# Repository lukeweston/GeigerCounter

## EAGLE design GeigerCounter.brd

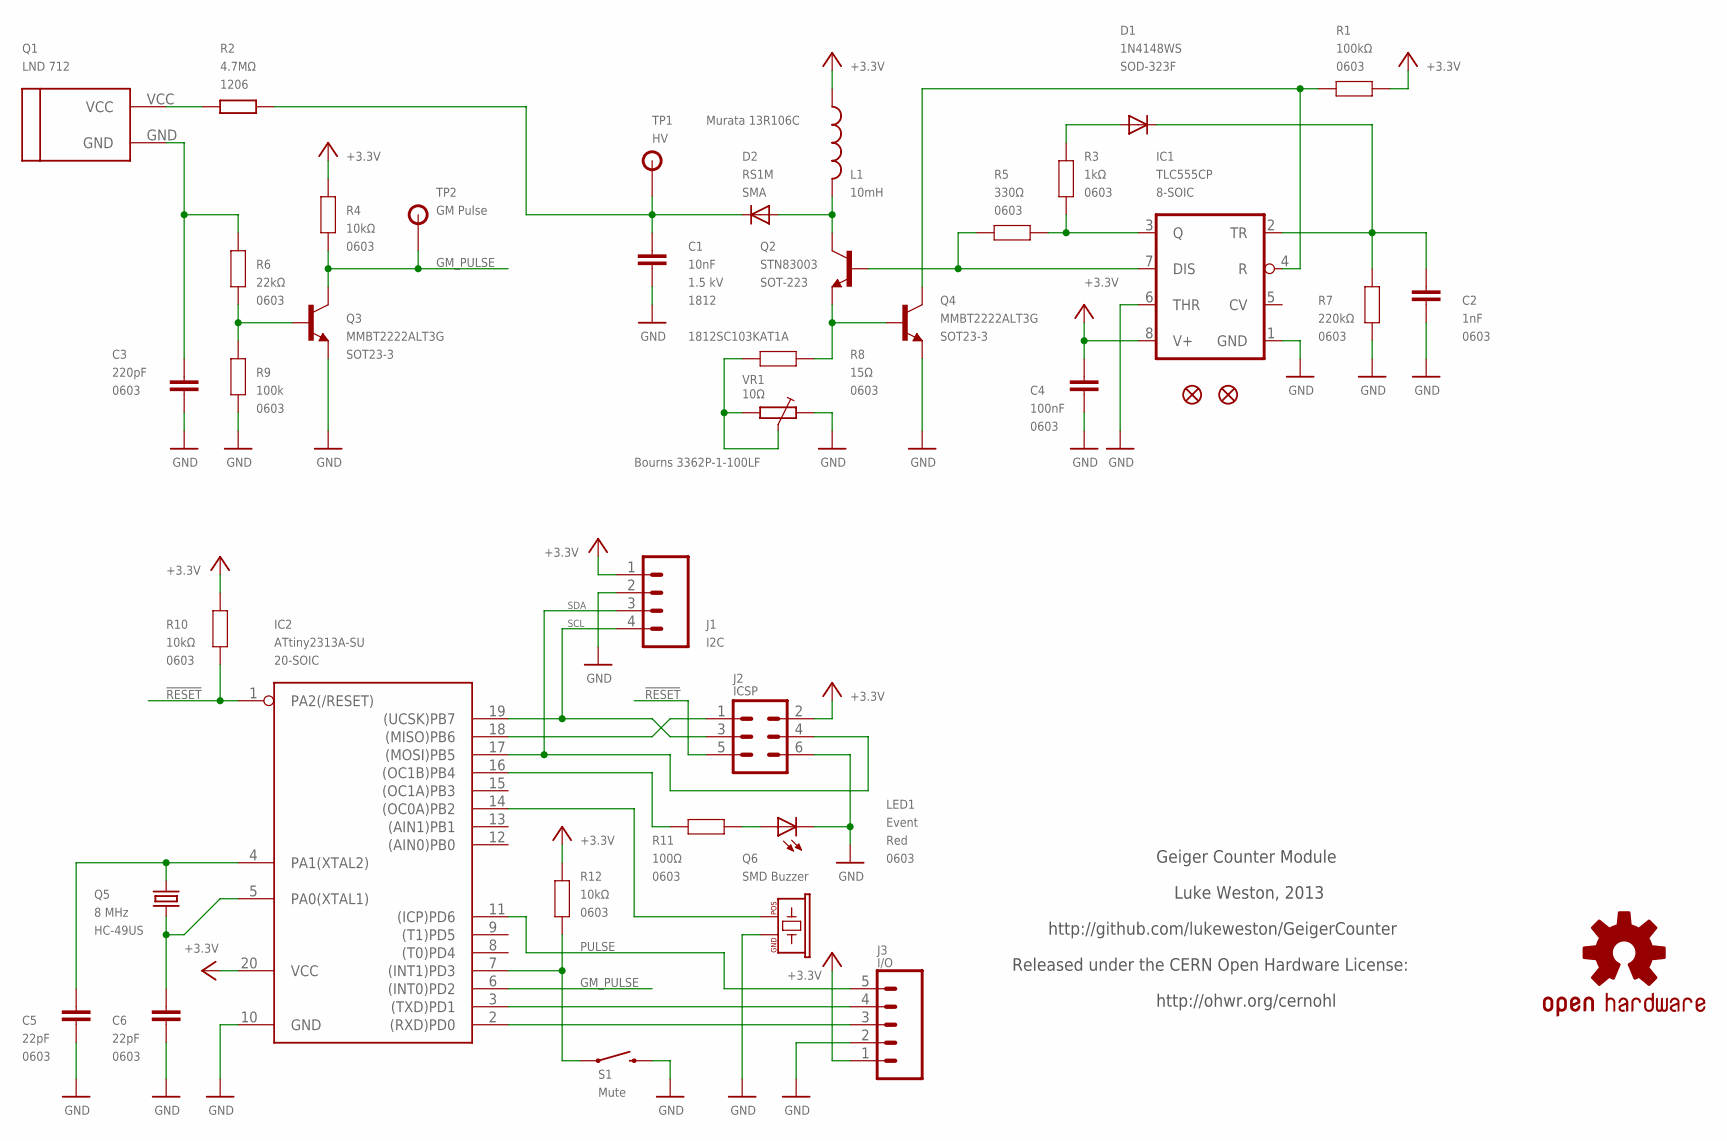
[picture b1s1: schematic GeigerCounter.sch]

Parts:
C1: 10nF; C1812; VOLTAGE 1.5 kV
C2: 1nF; 0603
C3: 220pF; 0603
C4: 100nF; 0603
C5, C6: 22pF; 0603
D1: 1N4148WS; SOD-323
D2: RS1M; DO214AC
IC1: TLC555CP; SO08
IC2: ATtiny2313A-SU; SO20L$
J1: I2C; 1X04
J2: ICSP; ICSP-6
J3: I/O; 1X05
JP1, JP2: FIDUCIALUFIDUCIAL; MICRO-FIDUCIAL
L1: 10mH; INDUCTOR-5.08
LED1: Event; LED-0603
Q1: LND 712; GEIGER_TUBE
Q2: STN83003; SOT223
Q3, Q4: MMBT2222ALT3G; SOT23
Q5: 8 MHz; HC49US
Q6: SMD Buzzer; BUZZER-12X12-SMT
R1: 100kΩ; 0603
R2: 4.7MΩ; R1206
R3: 1kΩ; 0603
R4, R10, R12: 10kΩ; 0603
R5: 330Ω; 0603
R6: 22kΩ; 0603
R7: 220kΩ; 0603
R8: 15Ω; 0603
R9: 100k; 0603
R11: 100Ω; 0603
S1: Mute; TACTILE_SWITCH_SMD
SY: OSHW-LOGOS; OSHW-LOGO-S
TP1: HV; TP_PTH
TP2: GM Pulse; TP_PTH
VR1: 10Ω; CT6

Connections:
!RESET: IC2.1 (PA2(/RESET)), J2.5, R10.1
+3V3: C4.1, IC1.8 (V+), IC2.20 (VCC), J1.1, J2.2, J3.1, L1.1, R1.1, R4.2, R10.2, R12.1
GM_PULSE: IC2.6 ((INT0)PD2), Q3.3 (C), R4.1, TP2.P$1
GND: C1.2, C2.2, C3.2, C4.2, C5.2, C6.2, IC1.1 (GND), IC1.6 (THR), IC2.10 (GND), J1.2, J2.6, J3.2, LED1.C, Q3.2 (E), Q4.2 (E), Q6.1 (GND), R7.1, R9.1, S1.3 (2), VR1.E
MUTE1: IC2.7 ((INT1)PD3), R12.2, S1.1
unnamed: Q1.VCC, R2.1
unnamed: IC1.7 (DIS), Q2.1 (B), R5.2
unnamed: IC1.4 (R), Q4.3 (C), R1.2
unnamed: IC2.2 ((RXD)PD0), J3.3
unnamed: IC2.3 ((TXD)PD1), J3.4
unnamed: C6.1, IC2.5 (PA0(XTAL1)), Q5.1
unnamed: C5.1, IC2.4 (PA1(XTAL2)), Q5.2
unnamed: IC2.18 ((MISO)PB6), J2.1
unnamed: IC2.16 ((OC1B)PB4), R11.2
unnamed: LED1.A, R11.1
unnamed: IC2.14 ((OC0A)PB2), Q6.2 (POS)
unnamed: IC1.3 (Q), R3.2, R5.1
unnamed: C3.1, Q1.GND, R6.2
unnamed: Q3.1 (B), R6.1, R9.2
unnamed: C2.1, D1.1 (C), IC1.2 (TR), R7.2
unnamed: D1.2 (A), R3.1
unnamed: Q2.3 (E), Q4.1 (B), R8.2
unnamed: R8.1, VR1.A, VR1.S
unnamed: D2.A, L1.2, Q2.4 (C)
unnamed: C1.1, D2.C, R2.2, TP1.P$1
PULSE: IC2.11 ((ICP)PD6), J3.5
SCL: IC2.19 ((UCSK)PB7), J1.4, J2.3
SDA: IC2.17 ((MOSI)PB5), J1.3, J2.4

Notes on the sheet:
Geiger Counter Module
Luke Weston, 2013
http://github.com/lukeweston/GeigerCounter
Released under the CERN Open Hardware License:
http://ohwr.org/cernohl

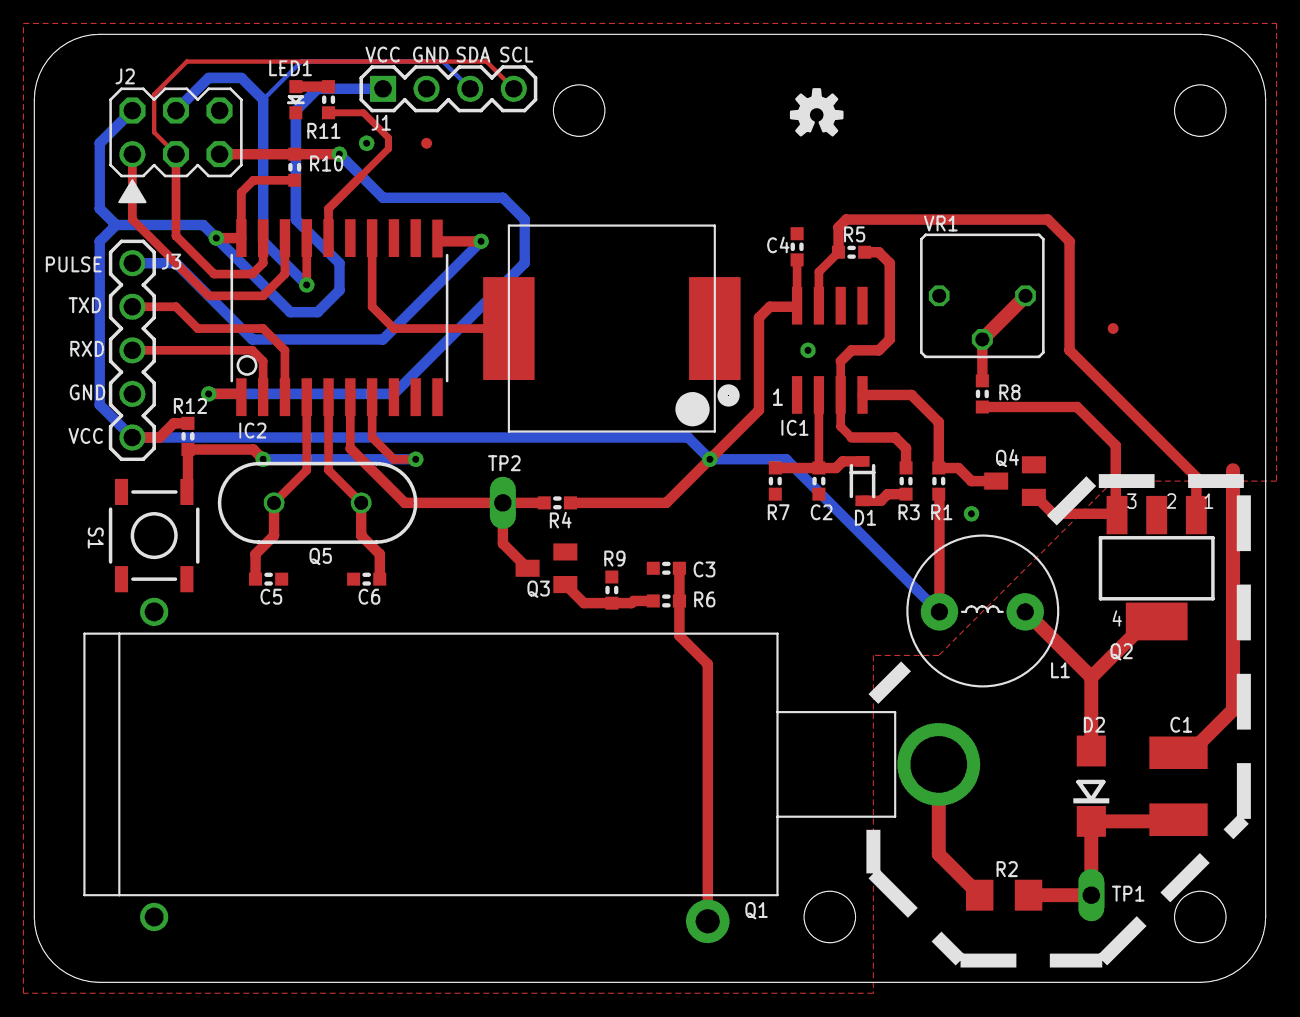
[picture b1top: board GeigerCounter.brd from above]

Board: 2 copper layers, 71.8 x 55.2 mm, 40 parts (0 on the bottom side), 28 nets.

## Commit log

2013-02-25 schematic and copper layout done, silkscreen and DRC not done yet.
2013-02-25 added license
2013-02-25 silkscreen tweaks
